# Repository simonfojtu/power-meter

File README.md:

POWER METER
===========

A Raspberry Pi HAT and software for real-time three phase real power monitoring.

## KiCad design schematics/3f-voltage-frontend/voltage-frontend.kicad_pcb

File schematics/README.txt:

Based on https://github.com/jonbuford/kicad-library/tree/RPi_HAT/template/raspberrrypi_hat
Raspberry PI HAT design guide
https://github.com/raspberrypi/hats/blob/master/designguide.md

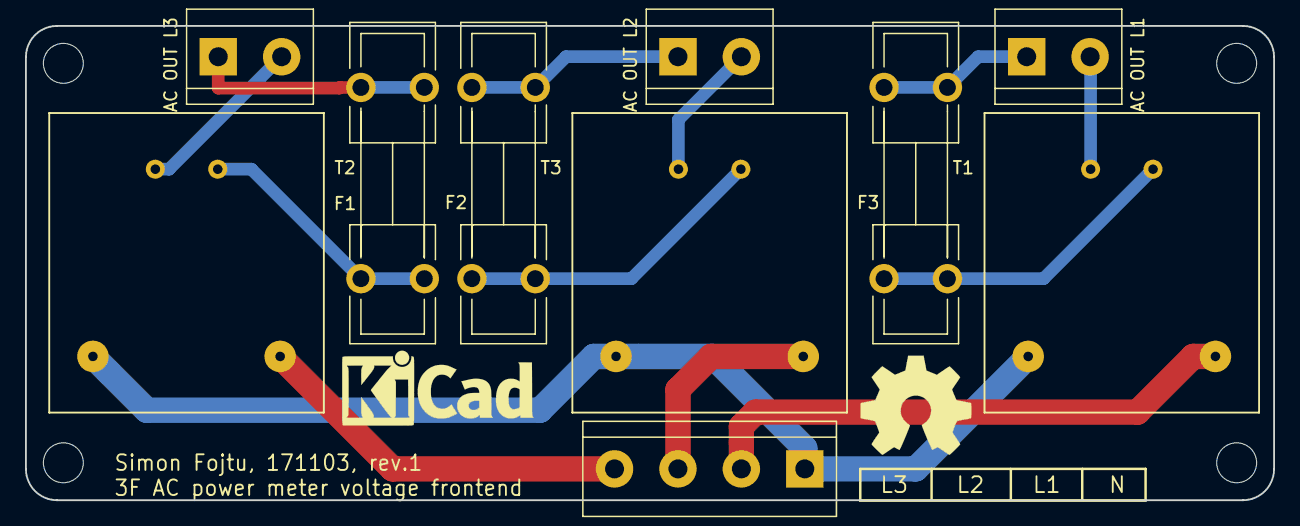
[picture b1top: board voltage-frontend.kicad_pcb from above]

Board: 2 copper layers, 100.0 x 38.0 mm, 14 parts (0 on the bottom side), 13 nets.

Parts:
F1, F2, F3: 3A; Fuseholder5x20_horiz_open_lateral_Type-II
P1: L3 L2 L1 N; bornier4
P2: AC OUT L1; bornier2
P3: AC OUT L3; bornier2
P4: AC OUT L2; bornier2
P5, P6, P7, P8: mounting hole; MountingHole_3.2mm_M3
T1, T2, T3: TRANSFO; BV-202-0154

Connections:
GND: P1.1, T1.2, T2.2, T3.2
unnamed: F1.1, T2.4
unnamed: F1.2, P3.1
unnamed: F2.1, T3.4
unnamed: F2.2, P4.1
unnamed: F3.1, T1.4
unnamed: F3.2, P2.1
unnamed: P1.2, T1.1
unnamed: P1.3, T3.1
unnamed: P1.4, T2.1
unnamed: P2.2, T1.3
unnamed: P3.2, T2.3
unnamed: P4.2, T3.3

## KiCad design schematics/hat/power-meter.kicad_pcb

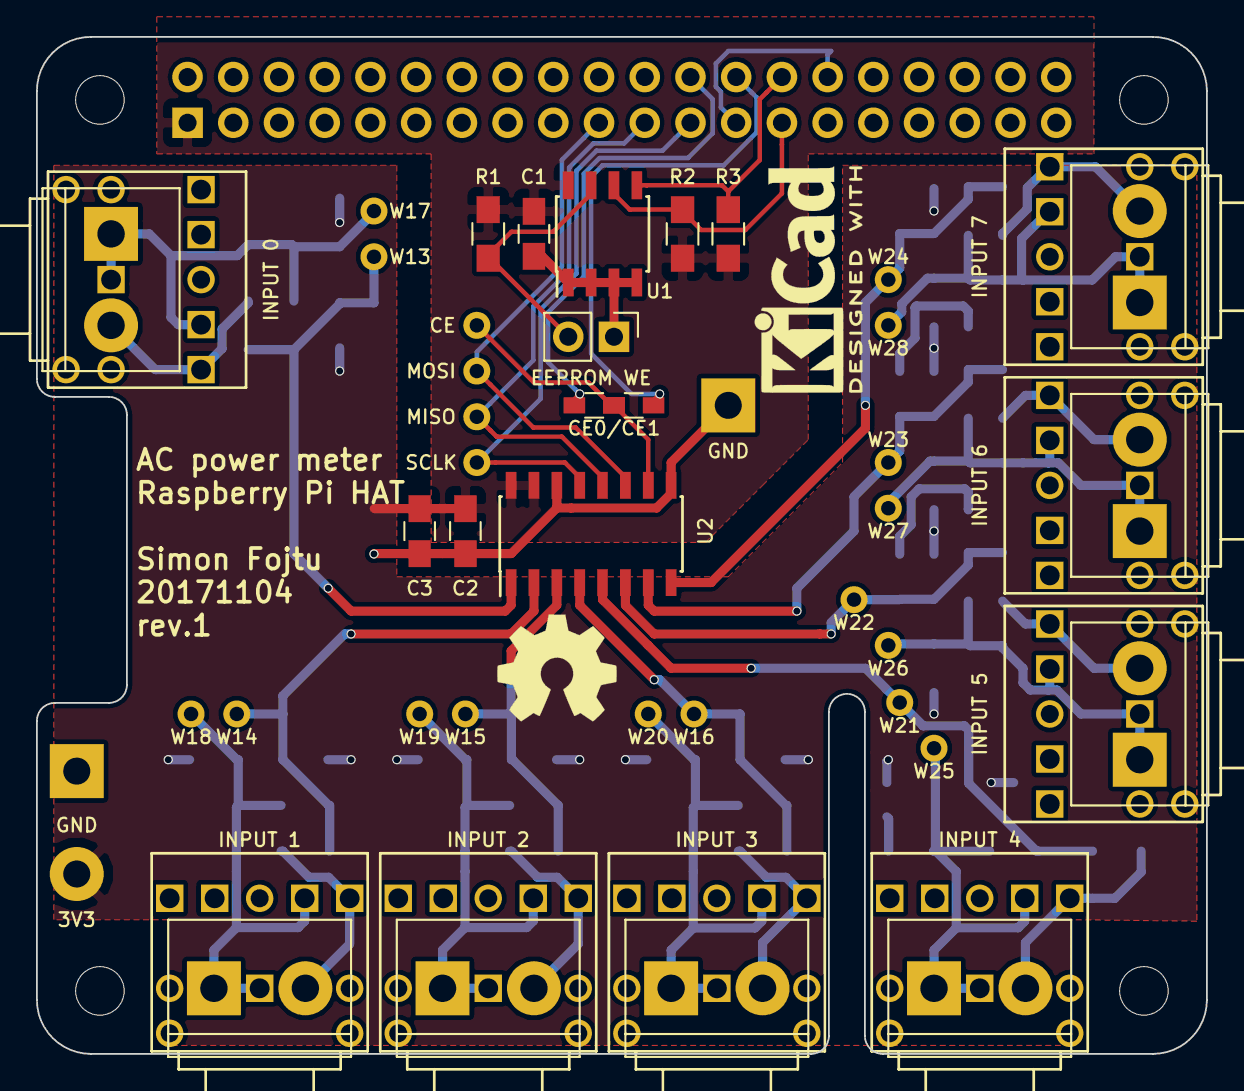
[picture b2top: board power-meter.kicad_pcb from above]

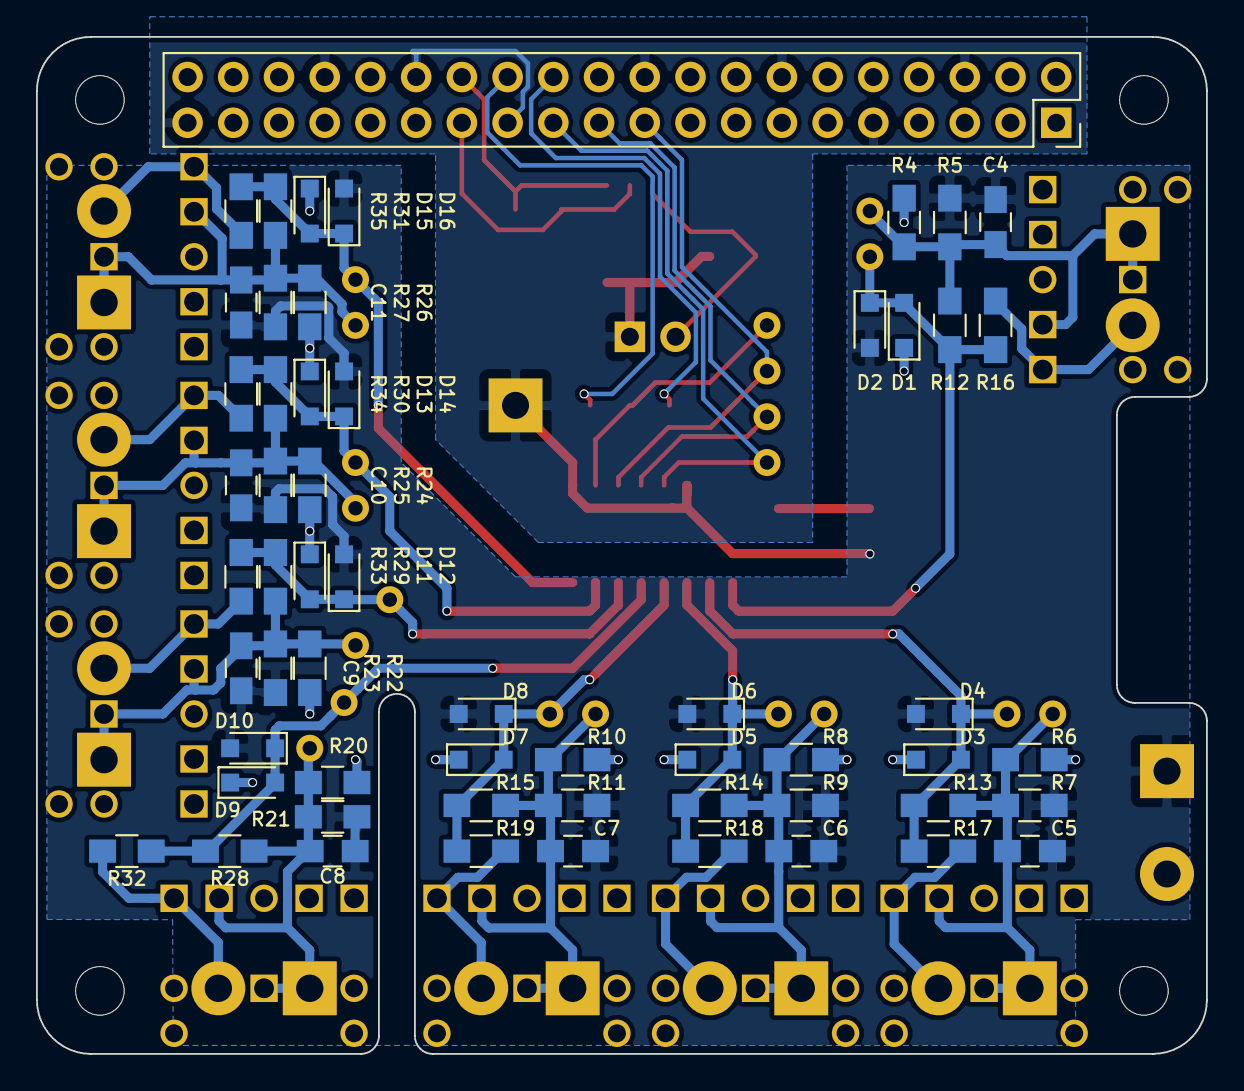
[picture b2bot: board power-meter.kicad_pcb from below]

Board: 2 copper layers, 65.0 x 56.5 mm, 113 parts (57 on the bottom side), 35 nets.

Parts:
C1, C2: 100n; C_0805_HandSoldering
C3: 220n; C_0805_HandSoldering
C4, C5, C6, C7, C8, C9, C10, C11: 10uF; C_0805_HandSoldering
D1, D2, D3, D4, D5, D6, D7, D8, D9, D10, D11, D12, D13, D14, D15, D16: BAS16J.115; D_SOD-323_HandSoldering
J1: EEPROM WE; Pin_Header_Straight_1x02_Pitch2.54mm
J2: 40HAT; Socket_Strip_Straight_2x20_Pitch2.54mm
P1, P2, P3, P4: 3mm mounting hole; MountingHole_2.7mm_M2.5
P5: INPUT 0; bornier2
P6: INPUT 1; bornier2
P7: INPUT 2; bornier2
P8: INPUT 3; bornier2
P9: INPUT 4; bornier2
P10: INPUT 5; bornier2
P11: INPUT 6; bornier2
P12: INPUT 7; bornier2
P13: OSHW LOGO; OSHW-Symbol_6.7x6mm_SilkScreen
P14: KICAD LOGO; KiCad-Logo2_6mm_SilkScreen
P15, P16, P17, P18, P19, P20, P21, P22: JC128
R1: 1k; R_0805_HandSoldering
R2, R3: 3.9K; R_0805_HandSoldering
R4, R5, R6, R7, R8, R9, R10, R11, R20, R21, R22, R23, R24, R25, R26, R27: 470k; R_0805_HandSoldering
R12, R13, R14, R15, R28, R29, R30, R31: R; R_0805_HandSoldering
R16, R17, R18, R19, R32, R33, R34, R35: 0R; R_0805_HandSoldering
R36, R37: R; R_0603_HandSoldering
U1: CAT24C32; SOIC-8_3.9x4.9mm_Pitch1.27mm
U2: MCP3008; SOIC-16_3.9x9.9mm_Pitch1.27mm
W1, W4: GND; Measurement_Point_Square-TH_Big
W3: SCLK; Measurement_Point_Round-TH_Small
W6: MISO; Measurement_Point_Round-TH_Small
W7: 3V3; Measurement_Point_Round-TH_Big
W9: MOSI; Measurement_Point_Round-TH_Small
W12: CE; Measurement_Point_Round-TH_Small
W13, W14, W15, W16, W17, W18, W19, W20, W21, W22, W23, W24, W25, W26, W27, W28: TEST_1P; Measurement_Point_Round-TH_Small

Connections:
+3V3: C1.1, C2.1, C3.1, D1.1, D3.1, D5.1, D7.1, D9.1, D11.1, D13.1, D15.1, J2.1, R1.2, R2.1, R3.1, R4.2, R6.2, R8.2, R10.2, R20.2, R22.2, R24.2, R26.2, U1.8, U2.15, U2.16, W7.1
/CE: R36.2, R37.1, U2.10, W12.1
/CE0: J2.24, R36.1
/CE1: J2.26, R37.2
/ID_SC_EEPROM: J2.28, R3.2, U1.5
/ID_SD_EEPROM: J2.27, R2.2, U1.6
/INPUT0: D1.2, D2.1, R12.1, R16.2, U2.1, W13.1
/INPUT1: D3.2, D4.1, R13.1, R17.2, U2.2, W14.1
/INPUT2: D5.2, D6.1, R14.1, R18.2, U2.3, W15.1
/INPUT3: D7.2, D8.1, R15.1, R19.2, U2.4, W16.1
/INPUT4: D9.2, D10.1, R28.1, R32.2, U2.5, W21.1
/INPUT5: D11.2, D12.1, R29.1, R33.2, U2.6, W22.1
/INPUT6: D13.2, D14.1, R30.1, R34.2, U2.7, W23.1
/INPUT7: D15.2, D16.1, R31.1, R35.2, U2.8, W24.1
/MISO: J2.21, U2.12, W6.1
/MOSI: J2.19, U2.11, W9.1
/SCLK: J2.23, U2.13, W3.1
GND: C1.2, C2.2, C3.2, C4.2, C5.2, C6.2, C7.2, C8.2, C9.2, C10.2, C11.2, D2.2, D4.2, D6.2, D8.2, D10.2, D12.2, D14.2, D16.2, J1.1, J2.6, J2.9, J2.14, J2.20, J2.25, J2.30, J2.34, J2.39, R5.2, R7.2, R9.2, R11.2, R21.2, R23.2, R25.2, R27.2, U1.1, U1.2, U1.3, U1.4, U2.9, U2.14, W1.1, W4.1
unnamed: C4.1, P5.1, P15.1, P15.3, R4.1, R5.1, R12.2, W17.1
unnamed: C5.1, P6.1, P16.1, P16.3, R6.1, R7.1, R13.2, W18.1
unnamed: C6.1, P7.1, P17.1, P17.3, R8.1, R9.1, R14.2, W19.1
unnamed: C7.1, P8.1, P18.1, P18.3, R10.1, R11.1, R15.2, W20.1
unnamed: C8.1, P9.1, P19.1, P19.3, R20.1, R21.1, R28.2, W25.1
unnamed: C9.1, P10.1, P20.1, P20.3, R22.1, R23.1, R29.2, W26.1
unnamed: C10.1, P11.1, P21.1, P21.3, R24.1, R25.1, R30.2, W27.1
unnamed: C11.1, P12.1, P22.1, P22.3, R26.1, R27.1, R31.2, W28.1
unnamed: J1.2, R1.1, U1.7
unnamed: P10.2, P20.2, R33.1
unnamed: P11.2, P21.2, R34.1
unnamed: P12.2, P22.2, R35.1
unnamed: P5.2, P15.2, R16.1
unnamed: P6.2, P16.2, R17.1
unnamed: P7.2, P17.2, R18.1
unnamed: P8.2, P18.2, R19.1
unnamed: P9.2, P19.2, R32.1

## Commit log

2017-10-03 Add README
2017-10-25 script to replicate working environment on the RPi
2017-10-25 Modified example from Adafruit's MCP3008 library
2017-10-25 rev.1 of the board
2017-10-25 fixup portability of schematics
2017-11-02 fixup - input connected to virtual ground when no jack connector is inserted
2017-11-02 fixup - updated README
2017-11-03 fixup - silkscreen labels position, terminal blocks footprint rotated
2017-11-03 Add voltage frontend schematics + pcb layout
2017-11-04 3F voltage frontend: add logo, revision, renaming a moving
2017-11-04 3F frontend - shrunk pcb
2017-11-07 Script to install common packages on a RPi.
2017-11-09 update install scripts
2017-11-09 Crude measurement of real power
2017-11-10 display vrms, irms, apparent power and power factor
2017-11-20 web pages; update readme; update python script
2017-11-20 Check for running rrdtool instance when plotting graphs and silently skip
2017-11-21 parametrizable input channels, cleanup
2017-11-21 renamed
2017-11-25 Script to run the power meter
2017-11-25 readme update
2018-01-18 3 phase setup, plot sum of power, last modified timestamp, measuring real and apparent power
2018-01-18 Added rrdtool and nginx to installed packages.
2018-01-20 Create LICENSE
